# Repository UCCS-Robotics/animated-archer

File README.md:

quadcopter
==========

This quadcopter will be designed to use localized sensor data to accuratly search and identify persons or objects of interest and interact with an operational base to efficiently complete the mission. The quadcopter must be able to perform in hostile environments and make path decisions within the defined mission parameters. Communication with the operational base will be kept to a minimum: telemetry, status, high-level commands, and video. The quadcopter must be able to adapt to changes in the operational environment and to physical damage/interaction to the vehicle.

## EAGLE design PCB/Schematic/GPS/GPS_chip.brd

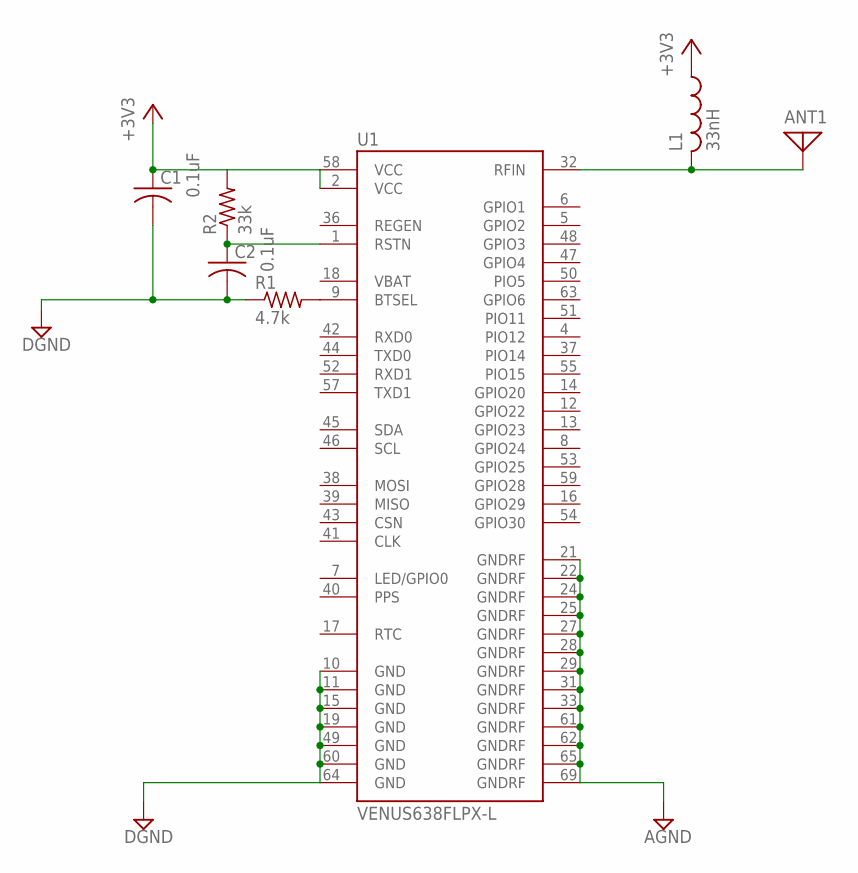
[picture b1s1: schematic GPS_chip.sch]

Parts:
ANT1: ANTENNA; PAD-01
C1, C2: C-USC0603; C0603
L1: 33nH; L4532P
R1: 4.7k; R0603
R2: 33k; R0603
U1: VENUS638FLPX-L; VENUS638FLPX

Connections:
+3V3: C1.1, L1.1, R2.2, U1.2 (VCC), U1.58 (VCC)
AGND: U1.21 (GNDRF), U1.22 (GNDRF), U1.24 (GNDRF), U1.25 (GNDRF), U1.27 (GNDRF), U1.28 (GNDRF), U1.29 (GNDRF), U1.31 (GNDRF), U1.33 (GNDRF), U1.61 (GNDRF), U1.62 (GNDRF), U1.65 (GNDRF), U1.69 (GNDRF)
DGND: C1.2, C2.2, R1.1, U1.10 (GND), U1.11 (GND), U1.15 (GND), U1.19 (GND), U1.49 (GND), U1.60 (GND), U1.64 (GND)
unnamed: R1.2, U1.9 (BTSEL)
unnamed: C2.1, R2.1, U1.1 (RSTN)
unnamed: ANT1.1, L1.2, U1.32 (RFIN)

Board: 2 copper layers, 7 parts (0 on the bottom side), 6 nets, no tracks yet.

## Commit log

2013-08-12 Create gh-pages branch via GitHub
2014-03-10 Removed non-development files
    In order to decrease the clone size, the non-dev files were
    removed.
2014-03-10 Added directory structure and requirements
2014-03-11 Updated GPS schematic
    Replaced resistors, capacitors, and inductors with SMD packages.
2014-03-13 FPGA Schematic and Library
    This commit adds a library with Xilinx FGPA parts for Eagle CAD and a
    Eagle schematic for the Spartan 6 FPGA.
2014-03-24 FPGA MUX addition
    Updated FPGA schematic to include multiplexer for JTAG programming and
    added library for Fairchild FST3257MTC multiplexer.
2014-03-30 Added the initial Altium project for the main board.
2014-04-03 Added the current main PCB schematic.
2014-04-04 Fixed the footprint on some capacitors.
2014-04-15 Added UML
2014-04-15 Updated template for UML
2014-04-16 Updated Device package
2014-04-16 Added more stuff
2014-04-18 Added sensor profiles
2014-04-20 Added template for makeProfile
2014-04-20 Added ui elements to makeProfile
2014-04-20 Added UI components
2014-04-21 Added initial USB device code
    Note, the code now requires libusb-1.0-0 to be present in the
    development environment.
2014-04-22 Added the USB I2C Teensyduino 3.1 code.
2014-04-22 Got the live graph working
2014-04-22 Threaded the incoming sensor data.
2014-04-23 Cleaned some code
2014-04-23 Cleaned working directory.
2014-04-23 Added auto rescaling for viewed frame.
2014-04-23 Added LCD init status.
2014-04-24 Added template code, and added chart features
    Added chart features to makeProfile
2014-04-24 Added device code for raw USB HID instead of serial.
2014-04-24 Fixed the USB HID I2C device firmware. Problem was the CRC module was not being clocked so it was waiting forever for the CRC calculation to complete to send in the next info packet.
2014-04-25 Temporarily removed accelsensor, removed libusb dependency
2014-04-25 Added the new I2C driver.
2014-04-25 Fixed some auto scaling issues
2014-04-25 Fixed a minor error in the LightSensor module.
2014-04-25 Fixed thread delete issue
2014-04-25 Fixed the light sensor to reconfigure when the device is plugged in again.
2014-04-27 Commented the main window code
    Also note: The rescale calculations for the x and y axes' are
    referenced on the other axes' values, thus if x is scaled up against
    y, then y scaled up against x, the y axis will scale against the
    updated x axis. This can cause the plot to 'zoom out' to an unreasonable
    scale fairly quickly.
2014-04-28 Added fake sensor for testing
2014-04-28 Added initial burst code to the USB I2C device firmware.
2014-04-28 Attempts to clean up errors when the device is unplugged.
2014-04-28 Added the changes for the burst program mode.
2014-04-29 Cleanup of the light sensor example.
2014-04-29 Fixed the autoscale again, manual yAxis scale broken
2014-04-29 Fixed the autoscale again, manual yAxis scale broken
    Also added a fake sensor.
2014-04-30 Initial fixes to the PCB schematic.
2014-04-30 Moved the ARM document.
2014-04-30 Started adding independent yAxis autoscale for multiple graphs.
2014-04-30 Added comments to yAxis autoscale.
2014-05-01 Fixed even more plot scaling issues.
2014-05-01 Added even more plot fixes. Also replaced LCD's with spinboxes.
2014-05-01 Made the transition between autoscale and not smoother.
    Also renamed processSensor to plotSensor.
2014-05-01 Implimented more plot features.
    Improved sliderBar-spinBox integration.
2014-05-01 Fixed pause/resume functionality and changed time recoriding style.
2014-05-01 Changed pause/resume button style
2014-05-01 Added a ton of interaction abilities.
    Among the additions: copy graph data (select graph, right click)
    Rename graph in legend (double click on name in legend)
    Move legend (right click on legend)
2014-05-01 Added copy image to clipboard functionality.
2014-05-01 Added feature creep.
    Added the ability for the legend rename to update the axis checkboxes.
2014-05-03 Rearranged and commented the code.
2014-05-03 Fixed sample speed when plot is running.
2014-05-03 Added save functionality (to csv).
2014-05-03 Fixed csv formatting.
2014-05-03 Added sample feature.
2014-05-06 Minor change of code
2014-05-06 Fixed "my" bad code.
2014-05-06 Fixed the ADC.
2014-05-06 Adjusted the ADC to change the update interval.
2014-05-07 Latest firmware.
2014-05-07 Removed LCD init code.
2014-05-07 Began refactoring sensor code.
2014-05-07 More refactoring.
    Yes, it still works (except maybe the plot autoscale).
2014-05-07 Yet another refactoring commit. (YARC)
2014-05-08 YARC
    Everything is broken! Halfway through critical conversion.
2014-05-08 YARC
    Limited functionality restored. Still refactoring sensors.
2014-05-09 YARC -> Commented code like a mad man
2014-05-09 YARC possibly finished sensor refactor
    Plotting functionality restored and tested with the US and the
    sudo sensor. The plotting method, however requires work.
2014-05-09 YARC -> Yup, forgot something
    Added the ability to take a limited number of samples. Also,
    FYI, none of the conversion functionality is working just yet.
2014-05-09 YARC -> Began refactoring the main plot
2014-05-09 YARC -> Changed the graph refs from indices to pointers
2014-05-10 YARC
2014-05-10 YARC -> This is getting complicated...
2014-05-10 YARC -> This is mostly a commit for amusement, checkout to see.
2014-05-10 YARC -> Minimal functionality restored.
    Plotter API is just about done.
2014-05-11 YARC -> Changed too many things to keep track of
    Even so, it works better now, for specifics, see
    the diff.
2014-05-30 Latest PCB changes.
2014-06-03 Added auto color, and made transition to US sensor work
2014-10-10 Fixed crc clash

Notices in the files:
parts and their libraries:
SparkFun-RF: Licensing: CC v3.0 Share-Alike You are welcome to use this library for commercial purposes.
